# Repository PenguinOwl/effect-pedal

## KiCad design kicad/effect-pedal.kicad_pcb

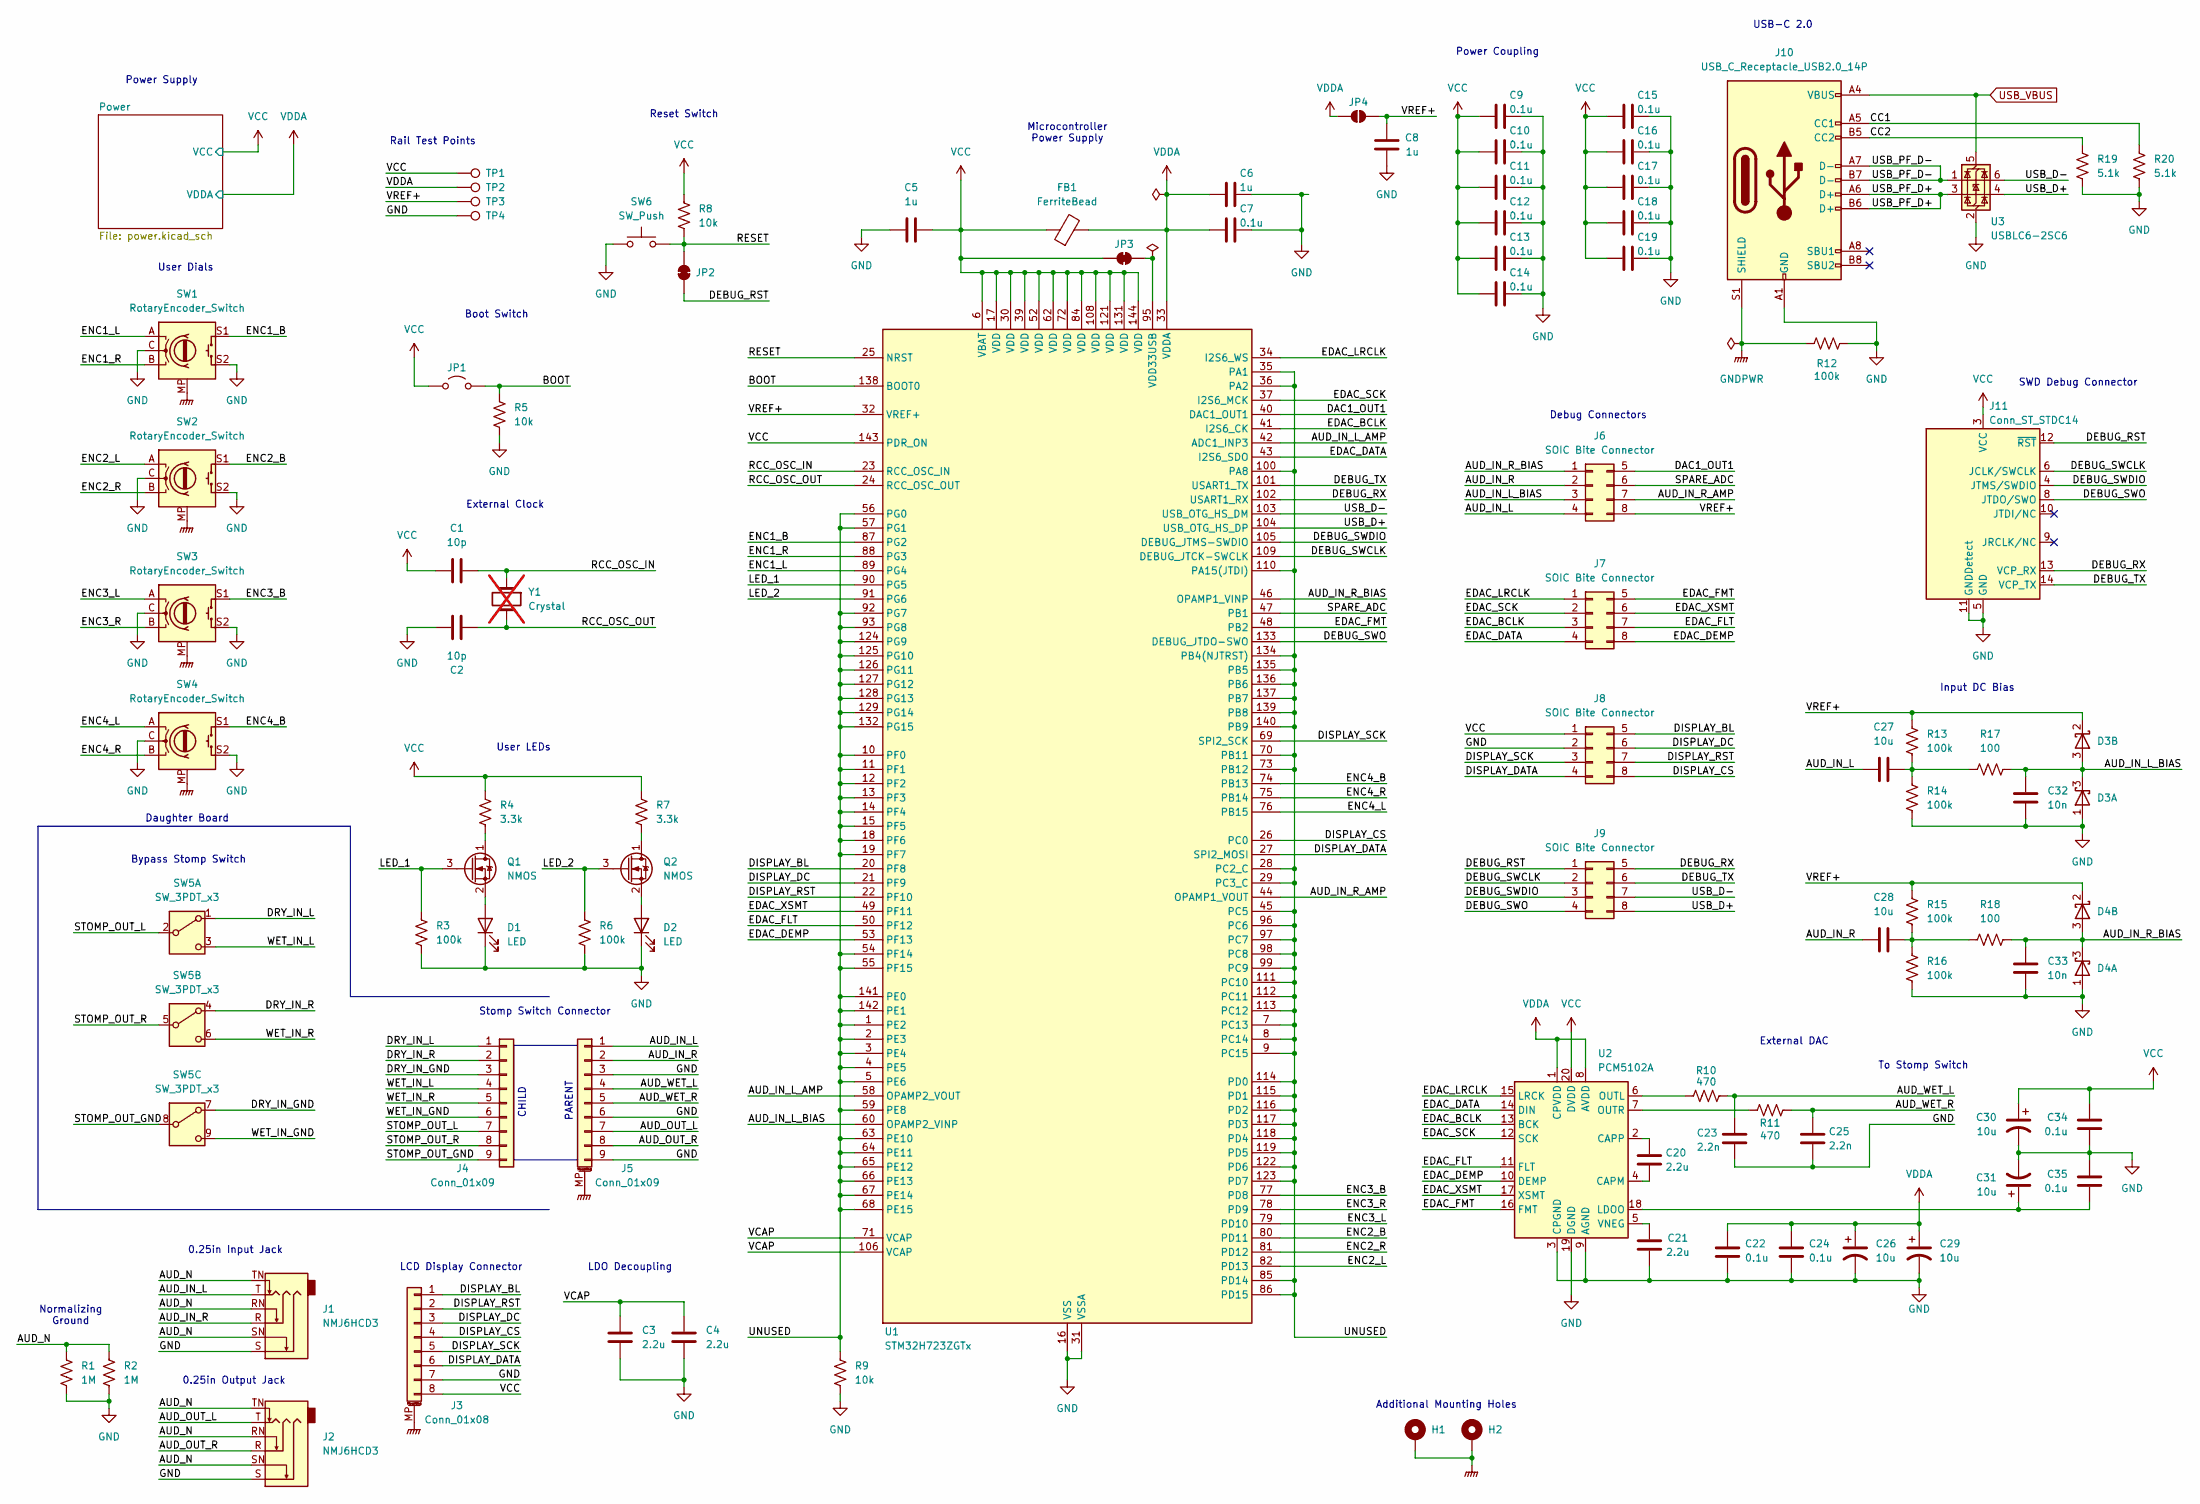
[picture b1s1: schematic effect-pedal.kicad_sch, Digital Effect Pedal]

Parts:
C1, C2: 10p; C_0603_1608Metric; Part KGM15ACG1E100KT
C3, C4, C20, C21: 2.2u; C_0603_1608Metric; Part Generic
C5, C6, C8: 1u; C_0603_1608Metric; Part Generic
C7, C9, C10, C11, C12, C13, C14, C15, C16, C17, C18, C19, C22, C24, C34, C35: 0.1u; C_0603_1608Metric; Part CL10B104KO8NNNC
C23, C25: 2.2n; C_0603_1608Metric; Part Generic
C26, C27, C28, C29, C30, C31: 10u; C_0603_1608Metric; Part Generic
C32, C33: 10n; C_0603_1608Metric; Part HMJ107BB7103KAHT
D1, D2: LED; LED_0805_2012Metric; Part LTST-C170KRKT
D3, D4: D_Schottky_Dual_Series_ACK_Split; TSOT-23; Part BAT54SFILM
FB1: FerriteBead; L_1206_3216Metric; Part CZP2BFTTE601P
H1, H2: MountingHole_Pad; MountingHole_2.2mm_M2_ISO7380_Pad
J1, J2: NMJ6HCD3; Jack_6.35mm_Neutrik_NMJ6HCD3_Horizontal; Part NMJ6HCD3
J3: Conn_01x08; Waveshare_2.4in_LCD; Part 10129380-908001BLF
J4: Conn_01x09; JST_XH_S9B-XH-A_1x09_P2.50mm_Horizontal; Part Generic
J5: Conn_01x09; JST_PH_S9B-PH-SM4-TB_1x09-1MP_P2.00mm_Horizontal; Part S9B-PH-SM4-TB
J6, J7, J8, J9: SOIC Bite Connector; SOIC_clipProgSmall; Part Generic
J10: USB_C_Receptacle_USB2.0_14P; USB_C_Receptacle_GCT_USB4110; Part USB4110-GF-A
J11: Conn_ST_STDC14; STDC14_Connector; Part 20021512-00014T1LF
JP1: Jumper_2_Open; TestPoint_2Pads_Pitch2.54mm_Drill0.8mm
JP2, JP3: SolderJumper_2_Bridged; SolderJumper-2_P1.3mm_Bridged2Bar_RoundedPad1.0x1.5mm
JP4: SolderJumper_2_Open; SolderJumper-2_P1.3mm_Open_TrianglePad1.0x1.5mm
Q1, Q2: NMOS; SOT-23; Part IRLML6344TRPBF
R1, R2: 1M; R_0603_1608Metric; Part Generic
R3, R6, R12, R13, R14, R15, R16: 100k; R_0603_1608Metric; Part Generic
R4, R7: 3.3k; R_0603_1608Metric; Part Generic
R5, R8, R9: 10k; R_0603_1608Metric; Part Generic
R10, R11: 470; R_0603_1608Metric; Part Generic
R17, R18: 100; R_0603_1608Metric; Part Generic
R19, R20: 5.1k; R_0603_1608Metric; Part Generic
SW1, SW2, SW3, SW4: RotaryEncoder_Switch; RotaryEncoder_Bourns_Vertical_PEC12R-3x17F-Sxxxx; Part PEC12R-4225F-S0024
SW5: SW_3PDT_x3
SW6: SW_Push; SW_Push_1P1T_NO_E-Switch_TL3301NxxxxxG; Part TS04-66-65-BK-260-SMT
TP1, TP2, TP3, TP4: TestPoint; TestPoint_Pad_2.0x2.0mm
U1: STM32H723ZGTx; LQFP-144_20x20mm_P0.5mm; Part STM32H723ZGT6
U2: PCM5102A; TSSOP-20_4.4x6.5mm_P0.65mm; Part PCM5102AQPWRQ1
U3: USBLC6-2SC6; SOT-23-6; Part USBLC6-2SC6
Y1: Crystal; Crystal_SMD_HC49-SD; not fitted

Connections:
/AUD_IN_L: C27.1, J1.T, J5.1, J6.4
/AUD_IN_L_AMP: U1.42 (ADC1_INP3), U1.58 (OPAMP2_VOUT)
/AUD_IN_L_BIAS: C32.2, D3.3 (K), J6.3, R17.2, U1.60 (OPAMP2_VINP)
/AUD_IN_R: C28.1, J1.R, J5.2, J6.2
/AUD_IN_R_AMP: J6.7, U1.44 (OPAMP1_VOUT)
/AUD_IN_R_BIAS: C33.2, D4.3 (K), J6.1, R18.2, U1.46 (OPAMP1_VINP)
/AUD_N: J1.RN, J1.SN, J1.TN, J2.RN, J2.SN, J2.TN, R1.1, R2.1
/AUD_OUT_L: J2.T, J5.7
/AUD_OUT_R: J2.R, J5.8
/AUD_WET_L: C23.2, J5.4, R10.1
/AUD_WET_R: C25.2, J5.5, R11.1
/BOOT: JP1.2 (B), R5.1, U1.138 (BOOT0)
/CC1: J10.A5 (CC1), R20.1
/CC2: J10.B5 (CC2), R19.1
/DAC1_OUT1: J6.5, U1.40 (DAC1_OUT1)
/DEBUG_RST: J9.1, J11.12 (~RST), JP2.1 (A)
/DEBUG_RX: J9.5, J11.13 (VCP_RX), U1.102 (USART1_RX)
/DEBUG_SWCLK: J9.2, J11.6 (JCLK/SWCLK), U1.109 (DEBUG_JTCK-SWCLK)
/DEBUG_SWDIO: J9.3, J11.4 (JTMS/SWDIO), U1.105 (DEBUG_JTMS-SWDIO)
/DEBUG_SWO: J9.4, J11.8 (JTDO/SWO), U1.133 (DEBUG_JTDO-SWO)
/DEBUG_TX: J9.6, J11.14 (VCP_TX), U1.101 (USART1_TX)
/DISPLAY_BL: J3.1, J8.5, U1.20 (PF8)
/DISPLAY_CS: J3.4, J8.8, U1.26 (PC0)
/DISPLAY_DATA: J3.6, J8.4, U1.27 (SPI2_MOSI)
/DISPLAY_DC: J3.3, J8.6, U1.21 (PF9)
/DISPLAY_RST: J3.2, J8.7, U1.22 (PF10)
/DISPLAY_SCK: J3.5, J8.3, U1.69 (SPI2_SCK)
/EDAC_BCLK: J7.3, U1.41 (I2S6_CK), U2.13 (BCK)
/EDAC_DATA: J7.4, U1.43 (I2S6_SDO), U2.14 (DIN)
/EDAC_DEMP: J7.8, U1.53 (PF13), U2.10 (DEMP)
/EDAC_FLT: J7.7, U1.50 (PF12), U2.11 (FLT)
/EDAC_FMT: J7.5, U1.48 (PB2), U2.16 (FMT)
/EDAC_LRCLK: J7.1, U1.34 (I2S6_WS), U2.15 (LRCK)
/EDAC_SCK: J7.2, U1.37 (I2S6_MCK), U2.12 (SCK)
/EDAC_XSMT: J7.6, U1.49 (PF11), U2.17 (XSMT)
/ENC1_B: SW1.S1, U1.87 (PG2)
/ENC1_L: SW1.A, U1.89 (PG4)
/ENC1_R: SW1.B, U1.88 (PG3)
/ENC2_B: SW2.S1, U1.80 (PD11)
/ENC2_L: SW2.A, U1.82 (PD13)
/ENC2_R: SW2.B, U1.81 (PD12)
/ENC3_B: SW3.S1, U1.77 (PD8)
/ENC3_L: SW3.A, U1.79 (PD10)
/ENC3_R: SW3.B, U1.78 (PD9)
/ENC4_B: SW4.S1, U1.74 (PB13)
/ENC4_L: SW4.A, U1.76 (PB15)
/ENC4_R: SW4.B, U1.75 (PB14)
/LED_1: Q1.3 (G), R3.1, U1.90 (PG5)
/LED_2: Q2.3 (G), R6.1, U1.91 (PG6)
/RCC_OSC_IN: C1.2, U1.23 (RCC_OSC_IN), Y1.1
/RCC_OSC_OUT: C2.1, U1.24 (RCC_OSC_OUT), Y1.2
/RESET: JP2.2 (B), R8.2, SW6.2, U1.25 (NRST)
/SPARE_ADC: J6.6, U1.47 (PB1)
/UNUSED: R9.1, U1.1 (PE2), U1.2 (PE3), U1.3 (PE4), U1.4 (PE5), U1.5 (PE6), U1.7 (PC13), U1.8 (PC14), U1.9 (PC15), U1.10 (PF0), U1.11 (PF1), U1.12 (PF2), U1.13 (PF3), U1.14 (PF4), U1.15 (PF5), U1.18 (PF6), U1.19 (PF7), U1.28 (PC2_C), U1.29 (PC3_C), U1.35 (PA1), U1.36 (PA2), U1.45 (PC5), U1.54 (PF14), U1.55 (PF15), U1.56 (PG0), U1.57 (PG1), U1.59 (PE8), U1.63 (PE10), U1.64 (PE11), U1.65 (PE12), U1.66 (PE13), U1.67 (PE14), U1.68 (PE15), U1.70 (PB11), U1.73 (PB12), U1.85 (PD14), U1.86 (PD15), U1.92 (PG7), U1.93 (PG8), U1.96 (PC6), U1.97 (PC7), U1.98 (PC8), U1.99 (PC9), U1.100 (PA8), U1.110 (PA15(JTDI)), U1.111 (PC10), U1.112 (PC11), U1.113 (PC12), U1.114 (PD0), U1.115 (PD1), U1.116 (PD2), U1.117 (PD3), U1.118 (PD4), U1.119 (PD5), U1.122 (PD6), U1.123 (PD7), U1.124 (PG9), U1.125 (PG10), U1.126 (PG11), U1.127 (PG12), U1.128 (PG13), U1.129 (PG14), U1.132 (PG15), U1.134 (PB4(NJTRST)), U1.135 (PB5), U1.136 (PB6), U1.137 (PB7), U1.139 (PB8), U1.140 (PB9), U1.141 (PE0), U1.142 (PE1)
/USB_D+: J9.8, U1.104 (USB_OTG_HS_DP), U3.4 (I/O2)
/USB_D-: J9.7, U1.103 (USB_OTG_HS_DM), U3.6 (I/O1)
/USB_PF_D+: J10.A6 (D+), J10.B6 (D+), U3.3 (I/O2)
/USB_PF_D-: J10.A7 (D-), J10.B7 (D-), U3.1 (I/O1)
/VCAP: C3.1, C4.1, U1.71 (VCAP), U1.106 (VCAP)
/VREF+: C8.2, D3.2 (K), D4.2 (K), J6.8, JP4.2 (B), R13.1, R15.1, TP3.1, U1.32 (VREF+)
GND: C2.2, C3.2, C4.2, C5.2, C6.2, C7.2, C8.1, C9.2, C10.2, C11.2, C12.2, C13.2, C14.2, C15.2, C16.2, C17.2, C18.2, C19.2, C21.1, C22.2, C23.1, C24.2, C25.1, C26.2, C29.2, C30.2, C31.2, C32.1, C33.1, C34.2, C35.1, D1.1 (K), D2.1 (K), D3.1 (A), D4.1 (A), J1.S, J2.S, J3.7, J5.3, J5.6, J5.9, J8.2, J10.A1 (GND), J10.A12 (GND), J10.B1 (GND), J10.B12 (GND), J11.5 (GND), J11.7 (GND), J11.11 (GNDDetect), R1.2, R2.2, R3.2, R5.2, R6.2, R9.2, R12.2, R14.2, R16.2, R19.2, R20.2, SW1.C, SW1.S2, SW2.C, SW2.S2, SW3.C, SW3.S2, SW4.C, SW4.S2, SW6.1, TP4.1, U1.16 (VSS), U1.31 (VSSA), U1.38 (VSS), U1.51 (VSS), U1.61 (VSS), U1.83 (VSS), U1.94 (VSS), U1.107 (VSS), U1.120 (VSS), U1.130 (VSS), U2.3 (CPGND), U2.9 (AGND), U2.19 (DGND), U3.2 (GND); also elsewhere on the board
GNDPWR: H1.1, H2.1, J3.MP (MountPin), J5.MP (MountPin), J10.S1 (SHIELD), R12.1, SW1.MP, SW2.MP, SW3.MP, SW4.MP; also elsewhere on the board
unnamed: C27.2, R13.2, R14.1, R17.1
unnamed: C28.2, R15.2, R16.1, R18.1
unnamed: D1.2 (A), Q1.2 (S)
unnamed: D2.2 (A), Q2.2 (S)
unnamed: J4.1, SW5.1 (A)
unnamed: J4.2, SW5.4 (A)
unnamed: J4.3, SW5.7 (A)
unnamed: J4.4, SW5.3 (C)
unnamed: J4.5, SW5.6 (C)
unnamed: J4.6, SW5.9 (C)
unnamed: J4.7, SW5.2 (B)
unnamed: J4.8, SW5.5 (B)
unnamed: J4.9, SW5.8 (B)
unnamed: JP3.2 (B), U1.95 (VDD33USB)
unnamed: Q1.1 (D), R4.2
unnamed: Q2.1 (D), R7.2
unnamed: C20.1, U2.4 (CAPM)
unnamed: C20.2, U2.2 (CAPP)
unnamed: C31.1, C35.2, U2.18 (LDOO)
unnamed: R10.2, U2.6 (OUTL)
unnamed: R11.2, U2.7 (OUTR)
unnamed: C21.2, U2.5 (VNEG)
USB_VBUS: J10.A4 (VBUS), J10.A9 (VBUS), J10.B4 (VBUS), J10.B9 (VBUS), U3.5 (VBUS); also elsewhere on the board
VCC: C1.1, C5.1, C9.1, C10.1, C11.1, C12.1, C13.1, C14.1, C15.1, C16.1, C17.1, C18.1, C19.1, C30.1, C34.1, FB1.1, J3.8, J8.1, J11.3 (VCC), JP1.1 (A), JP3.1 (A), R4.1, R7.1, R8.1, TP1.1, U1.6 (VBAT), U1.17 (VDD), U1.30 (VDD), U1.39 (VDD), U1.52 (VDD), U1.62 (VDD), U1.72 (VDD), U1.84 (VDD), U1.108 (VDD), U1.121 (VDD), U1.131 (VDD), U1.143 (PDR_ON), U1.144 (VDD), U2.20 (DVDD); also elsewhere on the board
VDDA: C6.1, C7.1, C22.1, C24.1, C26.1, C29.1, FB1.2, JP4.1 (A), TP2.1, U1.33 (VDDA), U2.1 (CPVDD), U2.8 (AVDD); also elsewhere on the board

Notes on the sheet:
Normalizing Ground
Input DC Bias
CHILD
Microcontroller Power Supply
Boot Switch
SWD Debug Connector
Additional Mounting Holes
Power Supply
External DAC
Stomp Switch Connector
Debug Connectors
PARENT
LCD Display Connector
0.25in Input Jack
Daughter Board
USB-C 2.0
Reset Switch
To Stomp Switch
External Clock
LDO Decoupling
User Dials
0.25in Output Jack
Bypass Stomp Switch
Power Coupling
User LEDs
Rail Test Points

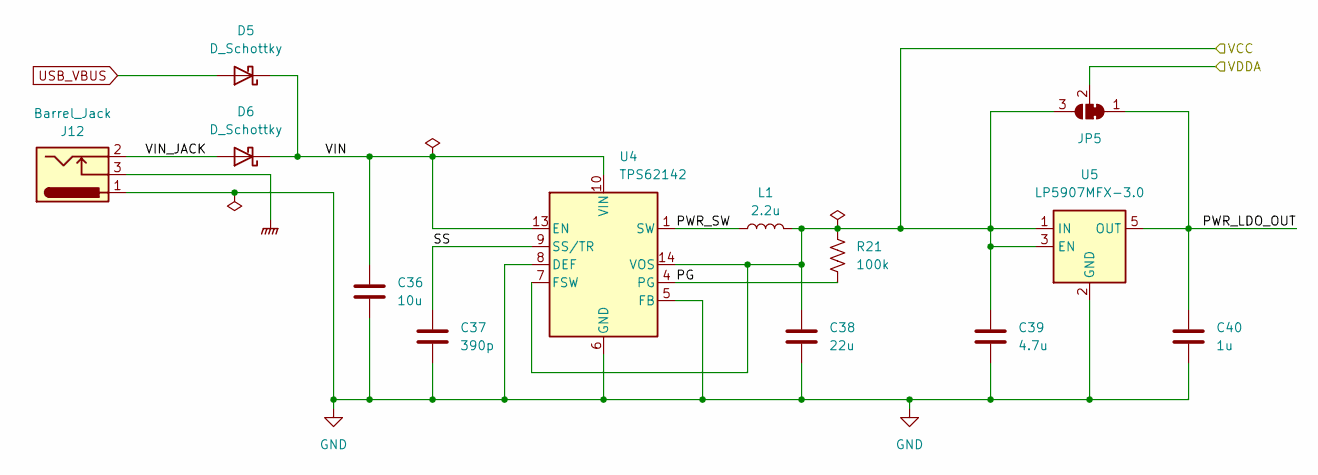
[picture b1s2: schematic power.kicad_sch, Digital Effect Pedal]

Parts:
C36: 10u; C_0603_1608Metric; Part Generic
C37: 390p; C_0603_1608Metric; Part C0603C391J5GAC
C38: 22u; C_0603_1608Metric; Part KAM21AT70J226KU
C39: 4.7u; C_0603_1608Metric; Part C1608X7S0G475M080AC
C40: 1u; C_0603_1608Metric; Part Generic
D5, D6: D_Schottky; D_SOD-323F; Part GSGP0240SD
J12: Barrel_Jack; CUI_PJ-002AH-SMT-TR; Part PJ-002AH-SMT-TR
JP5: SolderJumper_3_Bridged12; SolderJumper-3_P1.3mm_Bridged12_Pad1.0x1.5mm
L1: 2.2u; L_Vishay_IHLP-1212; Part MPX1D1250L2R2
R21: 100k; R_0603_1608Metric; Part Generic
U4: TPS62142; VQFN-16-1EP_3x3mm_P0.5mm_EP1.68x1.68mm_ThermalVias; Part TPS62142RGTR
U5: LP5907MFX-3.0; SOT-23-5; Part LP5907MFX-3.0

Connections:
/Power/PG: R21.2, U4.4 (PG)
/Power/PWR_LDO_OUT: C40.1, JP5.1 (A), U5.5 (OUT)
/Power/PWR_SW: L1.1, U4.1 (SW), U4.2 (SW), U4.3 (SW)
/Power/SS: C37.1, U4.9 (SS/TR)
/Power/VIN: C36.1, D5.1 (K), D6.1 (K), U4.10 (VIN), U4.11 (VIN), U4.12 (VIN), U4.13 (EN)
/Power/VIN_JACK: D6.2 (A), J12.2
GND: C36.2, C37.2, C38.2, C39.2, C40.2, J12.1, U4.5 (FB), U4.6 (GND), U4.8 (DEF), U4.15 (GND), U4.16 (GND), U4.17 (GND), U5.2 (GND); also elsewhere on the board
GNDPWR: J12.3; also elsewhere on the board
USB_VBUS: D5.2 (A); also elsewhere on the board
VCC: C38.1, C39.1, JP5.3 (B), L1.2, R21.1, U4.7 (FSW), U4.14 (VOS), U5.1 (IN), U5.3 (EN); also elsewhere on the board
VDDA: JP5.2 (C); also elsewhere on the board

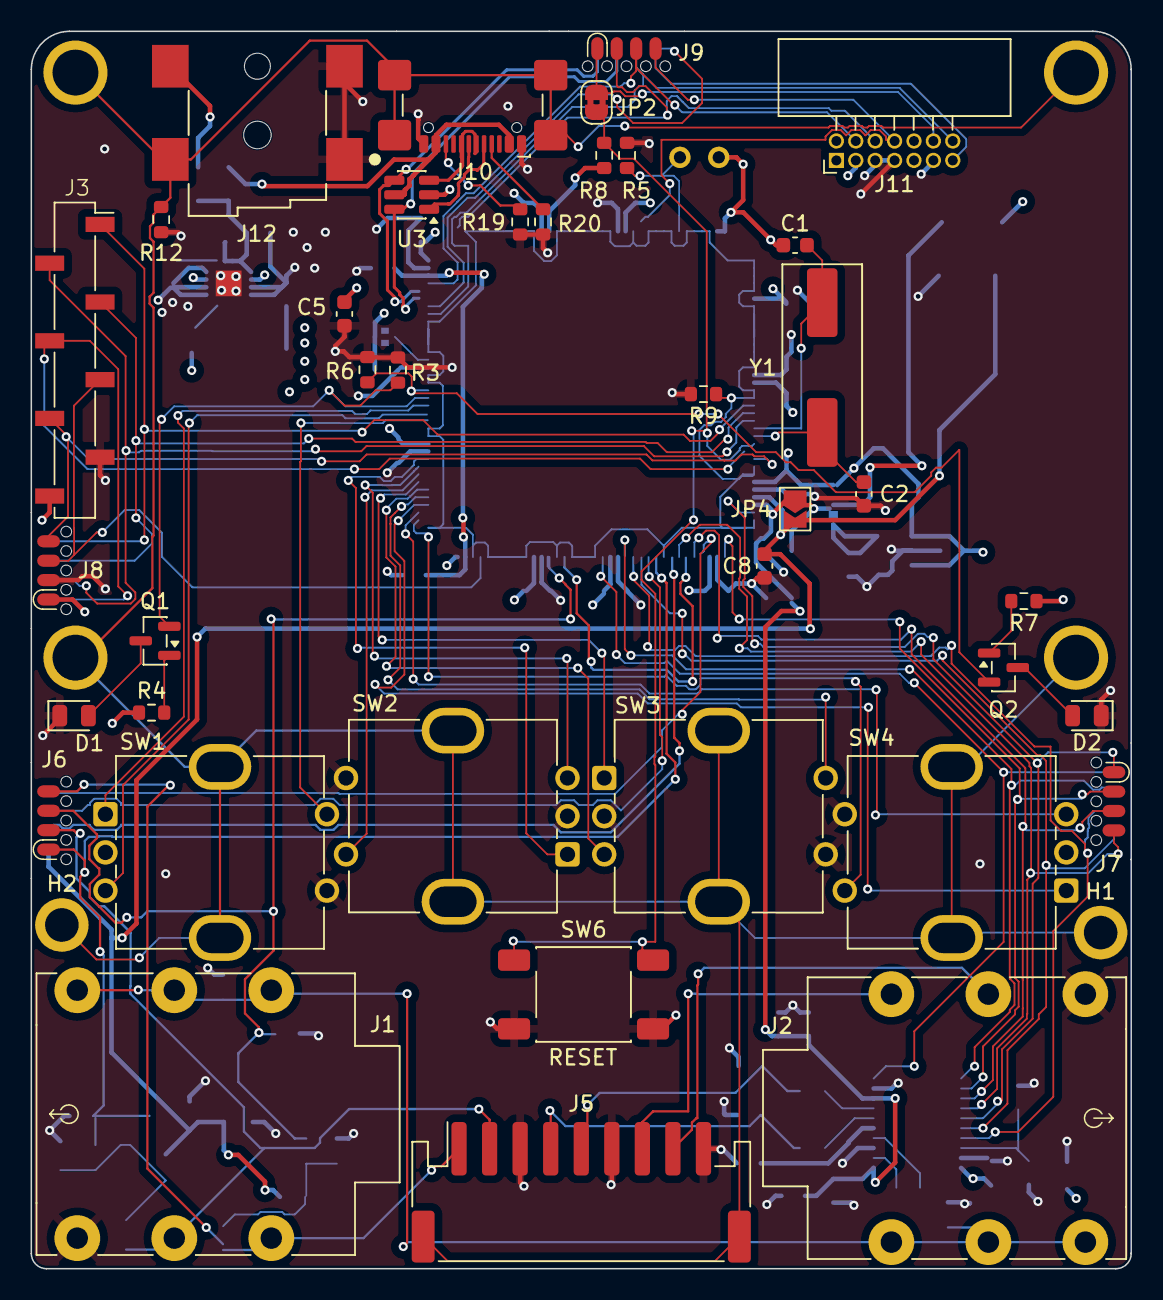
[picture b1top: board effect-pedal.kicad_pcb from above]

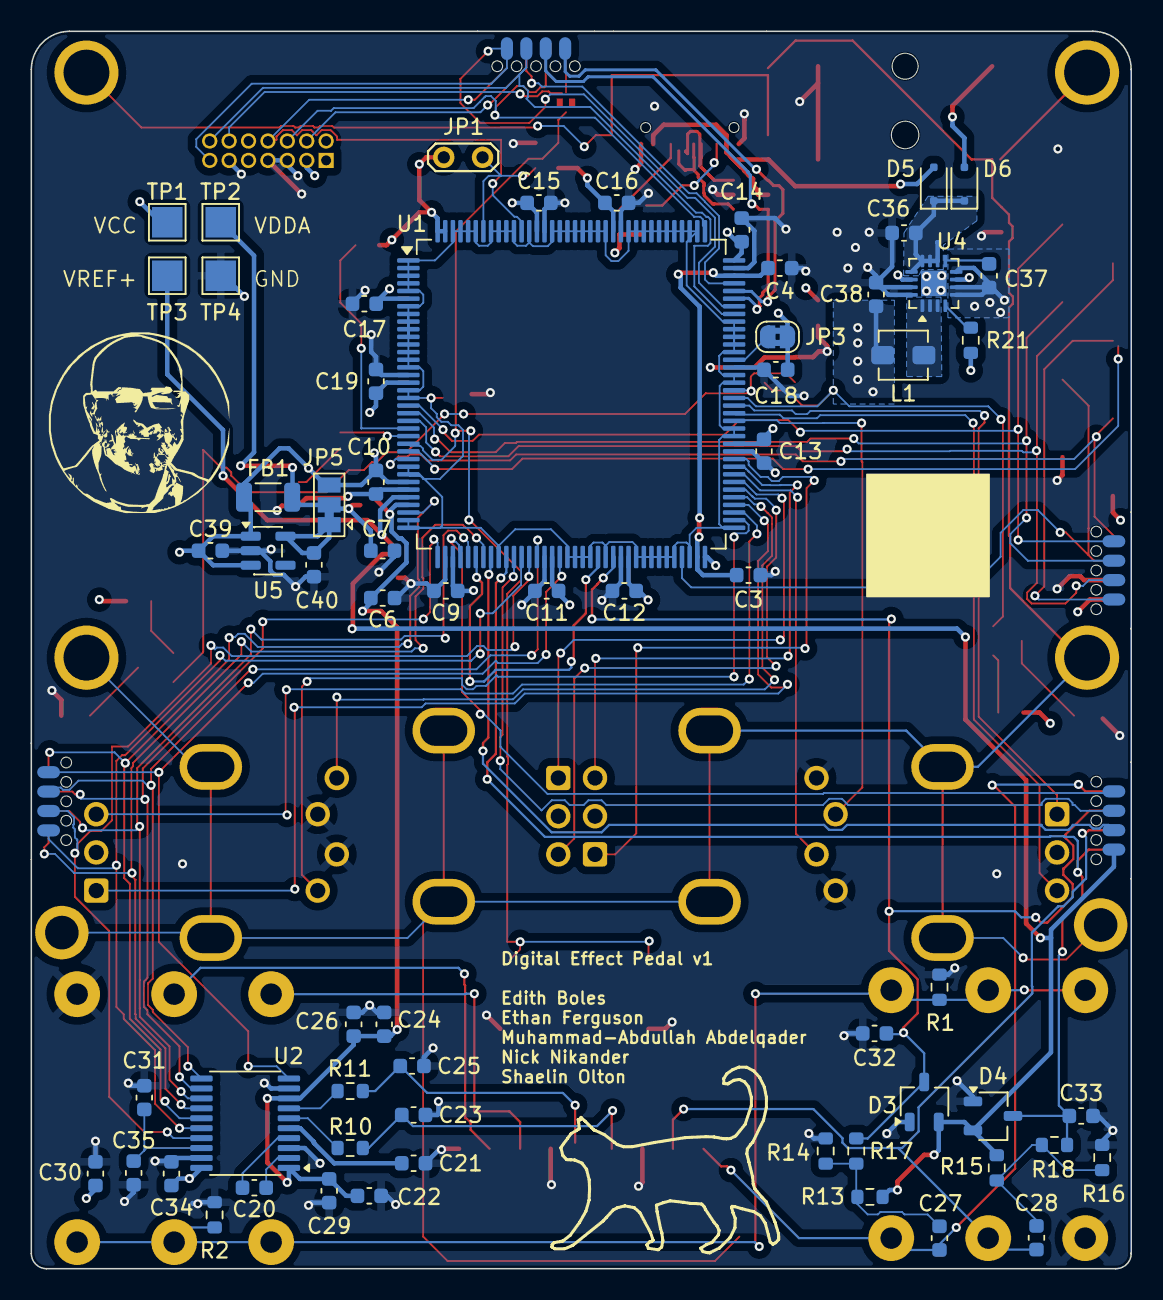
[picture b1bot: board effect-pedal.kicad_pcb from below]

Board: 4 copper layers, 72.0 x 81.0 mm, 104 parts (64 on the bottom side), 84 nets.

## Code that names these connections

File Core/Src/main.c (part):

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
void lcd_color_transfer_ready_cb(SPI_HandleTypeDef *hspi) {
	/* CS high */
	HAL_GPIO_WritePin(DISPLAY_CS_GPIO_Port, DISPLAY_CS_Pin, GPIO_PIN_SET);
	lcd_bus_busy = 0;
	lv_display_flush_ready(lcd_disp);
}
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			lcd_color_transfer_ready_cb);

	/* reset LCD */
	HAL_GPIO_WritePin(DISPLAY_RST_GPIO_Port, DISPLAY_RST_Pin, GPIO_PIN_RESET);
	HAL_Delay(100);
	HAL_GPIO_WritePin(DISPLAY_RST_GPIO_Port, DISPLAY_RST_Pin, GPIO_PIN_SET);
	HAL_Delay(100);

	HAL_GPIO_WritePin(DISPLAY_CS_GPIO_Port, DISPLAY_CS_Pin, GPIO_PIN_SET);
	HAL_GPIO_WritePin(DISPLAY_DC_GPIO_Port, DISPLAY_DC_Pin, GPIO_PIN_SET);

	return HAL_OK;
}
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	hspi2.Init.DataSize = SPI_DATASIZE_8BIT;
	HAL_SPI_Init(&hspi2);
	/* DCX low (command) */
	HAL_GPIO_WritePin(DISPLAY_DC_GPIO_Port, DISPLAY_DC_Pin, GPIO_PIN_RESET);
	/* CS low */
	HAL_GPIO_WritePin(DISPLAY_CS_GPIO_Port, DISPLAY_CS_Pin, GPIO_PIN_RESET);
	/* send command */
	if (HAL_SPI_Transmit(&hspi2, cmd, cmd_size, BUS_SPI2_POLL_TIMEOUT)
			== HAL_OK) {
		/* DCX high (data) */
		HAL_GPIO_WritePin(DISPLAY_DC_GPIO_Port, DISPLAY_DC_Pin, GPIO_PIN_SET);
		/* for short data blocks we use polling transfer */
		HAL_SPI_Transmit(&hspi2, (uint8_t*) param, (uint16_t) param_size,
				BUS_SPI2_POLL_TIMEOUT);
		/* CS high */
		HAL_GPIO_WritePin(DISPLAY_CS_GPIO_Port, DISPLAY_CS_Pin, GPIO_PIN_SET);
	}
}

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	hspi2.Init.DataSize = SPI_DATASIZE_8BIT;
	HAL_SPI_Init(&hspi2);
	/* DCX low (command) */
	HAL_GPIO_WritePin(DISPLAY_DC_GPIO_Port, DISPLAY_DC_Pin, GPIO_PIN_RESET);
	/* CS low */
	HAL_GPIO_WritePin(DISPLAY_CS_GPIO_Port, DISPLAY_CS_Pin, GPIO_PIN_RESET);
	/* send command */
	if (HAL_SPI_Transmit(&hspi2, cmd, cmd_size, BUS_SPI2_POLL_TIMEOUT)
			== HAL_OK) {
		/* DCX high (data) */
		HAL_GPIO_WritePin(DISPLAY_DC_GPIO_Port, DISPLAY_DC_Pin, GPIO_PIN_SET);
		/* for color data use DMA transfer */
		/* Set the SPI in 16-bit mode to match endianness */
		hspi2.Init.DataSize = SPI_DATASIZE_16BIT;
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  __HAL_RCC_GPIOD_CLK_ENABLE();

  /*Configure GPIO pin Output Level */
  HAL_GPIO_WritePin(GPIOF, DISPLAY_BL_Pin|DISPLAY_DC_Pin|DISPLAY_RST_Pin|EDAC_XSMT_Pin, GPIO_PIN_SET);

  /*Configure GPIO pin Output Level */
  HAL_GPIO_WritePin(DISPLAY_CS_GPIO_Port, DISPLAY_CS_Pin, GPIO_PIN_SET);

  /*Configure GPIO pin Output Level */
  HAL_GPIO_WritePin(EDAC_SCK_GPIO_Port, EDAC_SCK_Pin, GPIO_PIN_RESET);

  /*Configure GPIO pin Output Level */
  HAL_GPIO_WritePin(EDAC_FMT_GPIO_Port, EDAC_FMT_Pin, GPIO_PIN_RESET);

  /*Configure GPIO pin Output Level */
  HAL_GPIO_WritePin(GPIOF, EDAC_FLT_Pin|EDAC_DEMP_Pin, GPIO_PIN_RESET);

  /*Configure GPIO pin Output Level */
  HAL_GPIO_WritePin(GPIOG, LED_1_Pin|LED_2_Pin, GPIO_PIN_RESET);

  /*Configure GPIO pins : PE2 PE3 PE4 PE5
                           PE6 PE8 PE10 PE11
                           PE12 PE13 PE14 PE15
                           PE0 PE1 */
  GPIO_InitStruct.Pin = GPIO_PIN_2|GPIO_PIN_3|GPIO_PIN_4|GPIO_PIN_5
                          |GPIO_PIN_6|GPIO_PIN_8|GPIO_PIN_10|GPIO_PIN_11
                          |GPIO_PIN_12|GPIO_PIN_13|GPIO_PIN_14|GPIO_PIN_15
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  GPIO_InitStruct.Pull = GPIO_NOPULL;
  HAL_GPIO_Init(GPIOE, &GPIO_InitStruct);

  /*Configure GPIO pins : PC13 PC14 PC15 PC2
                           PC3 PC5 PC6 PC7
                           PC8 PC9 PC10 PC11
                           PC12 */
  GPIO_InitStruct.Pin = GPIO_PIN_13|GPIO_PIN_14|GPIO_PIN_15|GPIO_PIN_2
                          |GPIO_PIN_3|GPIO_PIN_5|GPIO_PIN_6|GPIO_PIN_7
                          |GPIO_PIN_8|GPIO_PIN_9|GPIO_PIN_10|GPIO_PIN_11
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  GPIO_InitStruct.Pull = GPIO_NOPULL;
  HAL_GPIO_Init(GPIOC, &GPIO_InitStruct);

  /*Configure GPIO pins : PF0 PF1 PF2 PF3
                           PF4 PF5 PF6 PF7
                           PF14 PF15 */
  GPIO_InitStruct.Pin = GPIO_PIN_0|GPIO_PIN_1|GPIO_PIN_2|GPIO_PIN_3
                          |GPIO_PIN_4|GPIO_PIN_5|GPIO_PIN_6|GPIO_PIN_7
                          |GPIO_PIN_14|GPIO_PIN_15;
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  GPIO_InitStruct.Pull = GPIO_NOPULL;
  HAL_GPIO_Init(GPIOF, &GPIO_InitStruct);

  /*Configure GPIO pins : DISPLAY_BL_Pin EDAC_XSMT_Pin EDAC_FLT_Pin EDAC_DEMP_Pin */
  GPIO_InitStruct.Pin = DISPLAY_BL_Pin|EDAC_XSMT_Pin|EDAC_FLT_Pin|EDAC_DEMP_Pin;
  GPIO_InitStruct.Mode = GPIO_MODE_OUTPUT_PP;
  GPIO_InitStruct.Pull = GPIO_NOPULL;
  GPIO_InitStruct.Speed = GPIO_SPEED_FREQ_LOW;
  HAL_GPIO_Init(GPIOF, &GPIO_InitStruct);

  /*Configure GPIO pin : DISPLAY_DC_Pin */
  GPIO_InitStruct.Pin = DISPLAY_DC_Pin;
  GPIO_InitStruct.Mode = GPIO_MODE_OUTPUT_PP;
  GPIO_InitStruct.Pull = GPIO_NOPULL;
  GPIO_InitStruct.Speed = GPIO_SPEED_FREQ_VERY_HIGH;
  HAL_GPIO_Init(DISPLAY_DC_GPIO_Port, &GPIO_InitStruct);

  /*Configure GPIO pin : DISPLAY_RST_Pin */
  GPIO_InitStruct.Pin = DISPLAY_RST_Pin;
  GPIO_InitStruct.Mode = GPIO_MODE_OUTPUT_PP;
  GPIO_InitStruct.Pull = GPIO_PULLUP;
  GPIO_InitStruct.Speed = GPIO_SPEED_FREQ_LOW;
  HAL_GPIO_Init(DISPLAY_RST_GPIO_Port, &GPIO_InitStruct);

  /*Configure GPIO pin : DISPLAY_CS_Pin */
  GPIO_InitStruct.Pin = DISPLAY_CS_Pin;
  GPIO_InitStruct.Mode = GPIO_MODE_OUTPUT_PP;
  GPIO_InitStruct.Pull = GPIO_NOPULL;
  GPIO_InitStruct.Speed = GPIO_SPEED_FREQ_VERY_HIGH;
  HAL_GPIO_Init(DISPLAY_CS_GPIO_Port, &GPIO_InitStruct);

  /*Configure GPIO pins : PA1 PA2 PA8 PA9
                           PA15 */
  GPIO_InitStruct.Pin = GPIO_PIN_1|GPIO_PIN_2|GPIO_PIN_8|GPIO_PIN_9
                          |GPIO_PIN_15;
  GPIO_InitStruct.Mode = GPIO_MODE_ANALOG;
  GPIO_InitStruct.Pull = GPIO_NOPULL;
  HAL_GPIO_Init(GPIOA, &GPIO_InitStruct);

  /*Configure GPIO pin : EDAC_SCK_Pin */
  GPIO_InitStruct.Pin = EDAC_SCK_Pin;
  GPIO_InitStruct.Mode = GPIO_MODE_OUTPUT_PP;
  GPIO_InitStruct.Pull = GPIO_PULLDOWN;
  GPIO_InitStruct.Speed = GPIO_SPEED_FREQ_LOW;
  HAL_GPIO_Init(EDAC_SCK_GPIO_Port, &GPIO_InitStruct);

  /*Configure GPIO pins : PB1 PB11 PB12 PB4
                           PB5 PB7 PB8 PB9 */
  GPIO_InitStruct.Pin = GPIO_PIN_1|GPIO_PIN_11|GPIO_PIN_12|GPIO_PIN_4
                          |GPIO_PIN_5|GPIO_PIN_7|GPIO_PIN_8|GPIO_PIN_9;
  GPIO_InitStruct.Mode = GPIO_MODE_ANALOG;
  GPIO_InitStruct.Pull = GPIO_NOPULL;
  HAL_GPIO_Init(GPIOB, &GPIO_InitStruct);

  /*Configure GPIO pin : EDAC_FMT_Pin */
  GPIO_InitStruct.Pin = EDAC_FMT_Pin;
  GPIO_InitStruct.Mode = GPIO_MODE_OUTPUT_PP;
  GPIO_InitStruct.Pull = GPIO_NOPULL;
  GPIO_InitStruct.Speed = GPIO_SPEED_FREQ_LOW;
  HAL_GPIO_Init(EDAC_FMT_GPIO_Port, &GPIO_InitStruct);

  /*Configure GPIO pins : PG0 PG1 PG7 PG8
                           PG9 PG10 PG11 PG12
                           PG13 PG14 PG15 */
  GPIO_InitStruct.Pin = GPIO_PIN_0|GPIO_PIN_1|GPIO_PIN_7|GPIO_PIN_8
                          |GPIO_PIN_9|GPIO_PIN_10|GPIO_PIN_11|GPIO_PIN_12
                          |GPIO_PIN_13|GPIO_PIN_14|GPIO_PIN_15;
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  GPIO_InitStruct.Pull = GPIO_NOPULL;
  HAL_GPIO_Init(GPIOG, &GPIO_InitStruct);

  /*Configure GPIO pins : ENC4_B_Pin ENC4_R_Pin ENC4_L_Pin */
  GPIO_InitStruct.Pin = ENC4_B_Pin|ENC4_R_Pin|ENC4_L_Pin;
  GPIO_InitStruct.Mode = GPIO_MODE_INPUT;
  GPIO_InitStruct.Pull = GPIO_PULLUP;
  HAL_GPIO_Init(GPIOB, &GPIO_InitStruct);

  /*Configure GPIO pin : ENC3_B_Pin */
  GPIO_InitStruct.Pin = ENC3_B_Pin;
  GPIO_InitStruct.Mode = GPIO_MODE_INPUT;
  GPIO_InitStruct.Pull = GPIO_NOPULL;
  HAL_GPIO_Init(ENC3_B_GPIO_Port, &GPIO_InitStruct);

  /*Configure GPIO pins : ENC3_R_Pin ENC3_L_Pin ENC2_B_Pin ENC2_R_Pin
                           ENC2_L_Pin */
  GPIO_InitStruct.Pin = ENC3_R_Pin|ENC3_L_Pin|ENC2_B_Pin|ENC2_R_Pin
                          |ENC2_L_Pin;
  GPIO_InitStruct.Mode = GPIO_MODE_INPUT;
  GPIO_InitStruct.Pull = GPIO_PULLUP;
  HAL_GPIO_Init(GPIOD, &GPIO_InitStruct);

  /*Configure GPIO pins : PD14 PD15 PD0 PD1
                           PD2 PD3 PD4 PD5
                           PD6 PD7 */
  GPIO_InitStruct.Pin = GPIO_PIN_14|GPIO_PIN_15|GPIO_PIN_0|GPIO_PIN_1
                          |GPIO_PIN_2|GPIO_PIN_3|GPIO_PIN_4|GPIO_PIN_5
                          |GPIO_PIN_6|GPIO_PIN_7;
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  GPIO_InitStruct.Pull = GPIO_NOPULL;
  HAL_GPIO_Init(GPIOD, &GPIO_InitStruct);

  /*Configure GPIO pins : ENC1_B_Pin ENC1_R_Pin ENC1_L_Pin */
  GPIO_InitStruct.Pin = ENC1_B_Pin|ENC1_R_Pin|ENC1_L_Pin;
  GPIO_InitStruct.Mode = GPIO_MODE_INPUT;
  GPIO_InitStruct.Pull = GPIO_PULLUP;
  HAL_GPIO_Init(GPIOG, &GPIO_InitStruct);

  /*Configure GPIO pins : LED_1_Pin LED_2_Pin */
  GPIO_InitStruct.Pin = LED_1_Pin|LED_2_Pin;
  GPIO_InitStruct.Mode = GPIO_MODE_OUTPUT_PP;
  GPIO_InitStruct.Pull = GPIO_NOPULL;
  GPIO_InitStruct.Speed = GPIO_SPEED_FREQ_LOW;
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
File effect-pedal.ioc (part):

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Mcu.Name=STM32H723ZGTx
Mcu.Package=LQFP144
Mcu.UserName=STM32H723ZGTx
PA0.GPIOParameters=GPIO_Label
PA0.GPIO_Label=EDAC_LRCLK
PA0.Mode=Half_Duplex_Master_Tx
PA0.Signal=I2S6_WS
PA10.Mode=Asynchronous
PA10.Signal=USART1_RX
PA11.Mode=Device_Only_FS
PA11.Signal=USB_OTG_HS_DM
PA12.Mode=Device_Only_FS
PA12.Signal=USB_OTG_HS_DP
PA13(JTMS/SWDIO).Mode=Trace_Asynchronous_SW
PA13(JTMS/SWDIO).Signal=DEBUG_JTMS-SWDIO
PA14(JTCK/SWCLK).Mode=Trace_Asynchronous_SW
PA14(JTCK/SWCLK).Signal=DEBUG_JTCK-SWCLK
PA3.GPIOParameters=GPIO_PuPd,GPIO_Label
PA3.GPIO_Label=EDAC_SCK
PA3.GPIO_PuPd=GPIO_PULLDOWN
PA3.Signal=GPIO_Output
PA4.Signal=COMP_DAC11_group
PA5.GPIOParameters=GPIO_Label
PA5.GPIO_Label=EDAC_BCLK
PA5.Mode=Half_Duplex_Master_Tx
PA5.Signal=I2S6_CK
PA6.Signal=ADCx_INP3
PA7.GPIOParameters=GPIO_Label
PA7.GPIO_Label=EDAC_DOUT
PA7.Mode=Half_Duplex_Master_Tx
PA7.Signal=I2S6_SDO
PB0.Mode=Follower
PB0.Signal=OPAMP1_VINP
PB10.GPIOParameters=GPIO_Speed,GPIO_PuPd,GPIO_Label
PB10.GPIO_Label=DISPLAY_SCK
PB10.GPIO_PuPd=GPIO_PULLDOWN
PB10.GPIO_Speed=GPIO_SPEED_FREQ_VERY_HIGH
PB10.Mode=TX_Only_Simplex_Unidirect_Master
PB10.Signal=SPI2_SCK
PB13.GPIOParameters=GPIO_PuPd,GPIO_Label
PB13.GPIO_Label=ENC4_B
PB13.GPIO_PuPd=GPIO_PULLUP
PB13.Signal=GPIO_Input
PB14.GPIOParameters=GPIO_PuPd,GPIO_Label
PB14.GPIO_Label=ENC4_R
PB14.GPIO_PuPd=GPIO_PULLUP
PB14.Signal=GPIO_Input
PB15.GPIOParameters=GPIO_PuPd,GPIO_Label
PB15.GPIO_Label=ENC4_L
PB15.GPIO_PuPd=GPIO_PULLUP
PB15.Signal=GPIO_Input
PB2.GPIOParameters=GPIO_Label
PB2.GPIO_Label=EDAC_FMT
PB2.Signal=GPIO_Output
PB3(JTDO/TRACESWO).Mode=Trace_Asynchronous_SW
PB3(JTDO/TRACESWO).Signal=DEBUG_JTDO-SWO
PB6.Mode=Asynchronous
PB6.Signal=USART1_TX
PC0.GPIOParameters=GPIO_Speed,PinState,GPIO_Label
PC0.GPIO_Label=DISPLAY_CS
PC0.GPIO_Speed=GPIO_SPEED_FREQ_VERY_HIGH
PC0.PinState=GPIO_PIN_SET
PC0.Signal=GPIO_Output
PC1.GPIOParameters=GPIO_Speed,GPIO_PuPd,GPIO_Label
PC1.GPIO_Label=DISPLAY_DATA
PC1.GPIO_PuPd=GPIO_PULLUP
PC1.GPIO_Speed=GPIO_SPEED_FREQ_VERY_HIGH
PC1.Mode=TX_Only_Simplex_Unidirect_Master
PC1.Signal=SPI2_MOSI
PC4.Mode=Follower
PC4.Signal=OPAMP1_VOUT
PD10.GPIOParameters=GPIO_PuPd,GPIO_Label
PD10.GPIO_Label=ENC3_L
PD10.GPIO_PuPd=GPIO_PULLUP
PD10.Signal=GPIO_Input
PD11.GPIOParameters=GPIO_PuPd,GPIO_Label
PD11.GPIO_Label=ENC2_B
PD11.GPIO_PuPd=GPIO_PULLUP
PD11.Signal=GPIO_Input
PD12.GPIOParameters=GPIO_PuPd,GPIO_Label
PD12.GPIO_Label=ENC2_R
PD12.GPIO_PuPd=GPIO_PULLUP
PD12.Signal=GPIO_Input
PD13.GPIOParameters=GPIO_PuPd,GPIO_Label
PD13.GPIO_Label=ENC2_L
PD13.GPIO_PuPd=GPIO_PULLUP
PD13.Signal=GPIO_Input
PD8.GPIOParameters=GPIO_Label
PD8.GPIO_Label=ENC3_B
PD8.Signal=GPIO_Input
PD9.GPIOParameters=GPIO_PuPd,GPIO_Label
PD9.GPIO_Label=ENC3_R
PD9.GPIO_PuPd=GPIO_PULLUP
PD9.Signal=GPIO_Input
PE7.Mode=Follower
PE7.Signal=OPAMP2_VOUT
PE9.Mode=Follower
PE9.Signal=OPAMP2_VINP
PF10.GPIOParameters=GPIO_Speed,PinState,GPIO_PuPd,GPIO_Label
PF10.GPIO_Label=DISPLAY_RST
PF10.GPIO_PuPd=GPIO_PULLUP
PF10.GPIO_Speed=GPIO_SPEED_FREQ_LOW
PF10.PinState=GPIO_PIN_SET
PF10.Signal=GPIO_Output
PF11.GPIOParameters=PinState,GPIO_Label
PF11.GPIO_Label=EDAC_XSMT
PF11.PinState=GPIO_PIN_SET
PF11.Signal=GPIO_Output
PF12.GPIOParameters=GPIO_Label
PF12.GPIO_Label=EDAC_FLT
PF12.Signal=GPIO_Output
PF13.GPIOParameters=GPIO_Label
PF13.GPIO_Label=EDAC_DEMP
PF13.Signal=GPIO_Output
PF8.GPIOParameters=PinState,GPIO_Label
PF8.GPIO_Label=DISPLAY_BL
PF8.PinState=GPIO_PIN_SET
PF8.Signal=GPIO_Output
PF9.GPIOParameters=GPIO_Speed,PinState,GPIO_Label
PF9.GPIO_Label=DISPLAY_DC
PF9.GPIO_Speed=GPIO_SPEED_FREQ_VERY_HIGH
PF9.PinState=GPIO_PIN_SET
PF9.Signal=GPIO_Output
PG2.GPIOParameters=GPIO_PuPd,GPIO_Label
PG2.GPIO_Label=ENC1_B
PG2.GPIO_PuPd=GPIO_PULLUP
PG2.Signal=GPIO_Input
PG3.GPIOParameters=GPIO_PuPd,GPIO_Label
PG3.GPIO_Label=ENC1_R
PG3.GPIO_PuPd=GPIO_PULLUP
PG3.Signal=GPIO_Input
PG4.GPIOParameters=GPIO_PuPd,GPIO_Label
PG4.GPIO_Label=ENC1_L
PG4.GPIO_PuPd=GPIO_PULLUP
PG4.Signal=GPIO_Input
PG5.GPIOParameters=GPIO_Label
PG5.GPIO_Label=LED_1
PG5.Signal=GPIO_Output
PG6.GPIOParameters=GPIO_Label
PG6.GPIO_Label=LED_2
PG6.Signal=GPIO_Output
PH0-OSC_IN.Signal=RCC_OSC_IN
PH1-OSC_OUT.Signal=RCC_OSC_OUT
RCC.SYSCLKFreq_VALUE=550000000
RCC.SYSCLKSource=RCC_SYSCLKSOURCE_PLLCLK
board=custom

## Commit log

2026-02-02 remake project
2026-02-04 Tune audio
2026-02-04 Implement lgvl
2026-02-04 Add encoder demo
2026-02-04 Volume demo
2026-02-04 Better vol display
2026-02-07 Add kicad project
2026-02-09 ive added trash
2026-02-11 Prep for schematic
2026-02-11 Start schematic
2026-02-11 Upload correct kicad project
2026-02-11 Labelled #pins
2026-02-13 wire up aud in jack
2026-02-13 Added FFT Library
    :)_
2026-02-13 start to DAC wiring
2026-02-13 Add power caps
2026-02-14 Clean up schematic
2026-02-16 Wiring on DAC pwr lines
2026-02-16 usb stuff & display label changes
2026-02-17 Finish basic schematic
2026-02-17 Start remapping of pins for I2S6
2026-02-17 Finish schematic and start assigning footprints
2026-02-18 Prodfiles for stomp
2026-02-18 DNP markers
2026-02-18 Add more part numbers and VDDA regulator
2026-02-18 Add more parts
2026-02-19 Update firmware to match new pinout
2026-02-19 Update pinout for startup state
2026-02-19 Vol is now Volume
    :(
2026-02-19 Finish part sourcing and start PCB layout
2026-02-20 Finish schematic
2026-02-21 Setup for production
2026-02-21 Background graph
2026-02-26 Making a snapshot for myself before I make changes in Cubemx
2026-02-27 Plot schematic pdf
2026-02-28 Add ibom
2026-03-01 Support the board and BDMA
2026-03-01 Remove debug noise scaling
2026-03-02 State of the 'Q
2026-03-02 Update FFT to read from dac
2026-03-03 Added Delay Effect
    Defined the delay settings, allocated delay buffer, added feedback and mix parameters, added process_audio_fft function which creates a delay loop, called from normal process_audio function.
    Note * Changed ADC1 to 1 channel; Number of conversions = 1. With 2 channels the ADC values were messed up and the audio output was turning on/off or ticking
2026-03-03 lose
2026-03-03 Revert "Added Delay Effect"
    This reverts commit 31df361a8eaab517668d6a041f7feeb787219462.
2026-03-03 Revert ADC1 back to 2 Channels
    Number of conversions = 2, Rank 1:Channel 3, Rank 2:Channel 4. DAC buffer address 0/1 are read from ADC buffer 0. DAC buffer address 2/3 are read from ADC buffer address 2.
2026-03-03 Added FFT Timer
2026-03-04 Updated to show > 20kHz
2026-03-06 Tune EQ display
2026-03-07 case
2026-03-13 Add basic encoder demo
2026-03-13 [WIP] Add encoder functions for effect
2026-03-13 Finish for final demo

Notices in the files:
Core/Src/main.c:
Copyright (c) 2026 STMicroelectronics.
All rights reserved.
This software is licensed under terms that can be found in the LICENSE file
